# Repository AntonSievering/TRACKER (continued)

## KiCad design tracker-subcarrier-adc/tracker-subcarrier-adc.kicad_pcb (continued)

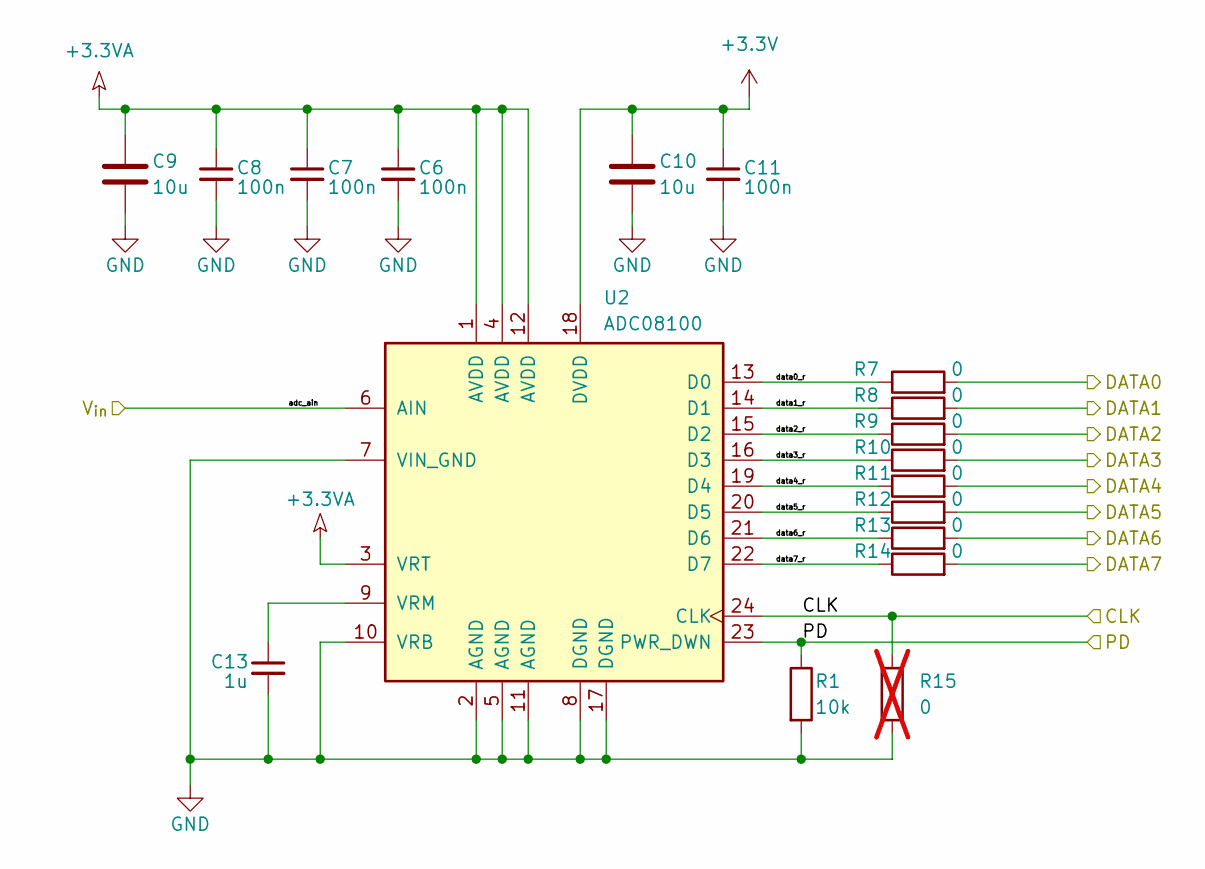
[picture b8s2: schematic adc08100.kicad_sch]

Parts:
C6, C7, C8, C11: 100n; C_0603_1608Metric
C9, C10: 10u; C_0805_2012Metric
C13: 1u; C_0603_1608Metric
R1: 10k; R_0603_1608Metric
R7, R8, R9, R10, R11, R12, R13, R14: 0; R_0603_1608Metric
R15: 0; R_0603_1608Metric; not fitted
U2: ADC08100; TSSOP-24_4.4x7.8mm_P0.65mm; MPN ADC08100CIMTCX/NOPB

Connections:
+3.3V: C10.1, C11.1, U2.18 (DVDD); also elsewhere on the board
+3.3VA: C6.1, C7.1, C8.1, C9.1, U2.1 (AVDD), U2.3 (VRT), U2.4 (AVDD), U2.12 (AVDD); also elsewhere on the board
/ADC I/adc_ain: U2.6 (AIN); also elsewhere on the board
/ADC I/data0_r: R7.1, U2.13 (D0)
/ADC I/data1_r: R8.1, U2.14 (D1)
/ADC I/data2_r: R9.1, U2.15 (D2)
/ADC I/data3_r: R10.1, U2.16 (D3)
/ADC I/data4_r: R11.1, U2.19 (D4)
/ADC I/data5_r: R12.1, U2.20 (D5)
/ADC I/data6_r: R13.1, U2.21 (D6)
/ADC I/data7_r: R14.1, U2.22 (D7)
/IO_PIN_1: R7.2; also elsewhere on the board
/IO_PIN_2: R8.2; also elsewhere on the board
/IO_PIN_3: R9.2; also elsewhere on the board
/IO_PIN_4: R10.2; also elsewhere on the board
/IO_PIN_5: R11.2; also elsewhere on the board
/IO_PIN_7: R12.2; also elsewhere on the board
/IO_PIN_8: R13.2; also elsewhere on the board
/IO_PIN_9: R14.2; also elsewhere on the board
/IO_PIN_10: R1.1, U2.23 (PWR_DWN); also elsewhere on the board
/IO_PIN_MRCC_25: R15.1, U2.24 (CLK); also elsewhere on the board
GND: C6.2, C7.2, C8.2, C9.2, C10.2, C11.2, C13.2, R1.2, R15.2, U2.2 (AGND), U2.5 (AGND), U2.7 (VIN_GND), U2.8 (DGND), U2.10 (VRB), U2.11 (AGND), U2.17 (DGND); also elsewhere on the board
unnamed: C13.1, U2.9 (VRM)

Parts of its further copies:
C12, C18: 10u; C_0805_2012Metric
C14, C16, C17, C19: 100n; C_0603_1608Metric
C15: 1u; C_0603_1608Metric
R2: 10k; R_0603_1608Metric
R3: 0; R_0603_1608Metric; not fitted
R4, R5, R6, R18, R19, R20, R21, R22: 0; R_0603_1608Metric
U3: ADC08100; TSSOP-24_4.4x7.8mm_P0.65mm; MPN ADC08100CIMTCX/NOPB

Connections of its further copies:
+3.3V: C18.1, C19.1, U3.18 (DVDD); also elsewhere on the board
+3.3VA: C12.1, C14.1, C16.1, C17.1, U3.1 (AVDD), U3.3 (VRT), U3.4 (AVDD), U3.12 (AVDD); also elsewhere on the board
/ADC Q/adc_ain: U3.6 (AIN); also elsewhere on the board
/ADC Q/data0_r: R4.1, U3.13 (D0)
/ADC Q/data1_r: R5.1, U3.14 (D1)
/ADC Q/data2_r: R6.1, U3.15 (D2)
/ADC Q/data3_r: R18.1, U3.16 (D3)
/ADC Q/data4_r: R19.1, U3.19 (D4)
/ADC Q/data5_r: R20.1, U3.20 (D5)
/ADC Q/data6_r: R21.1, U3.21 (D6)
/ADC Q/data7_r: R22.1, U3.22 (D7)
/IO_PIN_12: R4.2; also elsewhere on the board
/IO_PIN_13: R5.2; also elsewhere on the board
/IO_PIN_14: R6.2; also elsewhere on the board
/IO_PIN_15: R18.2; also elsewhere on the board
/IO_PIN_16: R19.2; also elsewhere on the board
/IO_PIN_17: R20.2; also elsewhere on the board
/IO_PIN_18: R21.2; also elsewhere on the board
/IO_PIN_19: R22.2; also elsewhere on the board
/IO_PIN_20: R2.1, U3.23 (PWR_DWN); also elsewhere on the board
/IO_PIN_MRCC_26: R3.1, U3.24 (CLK); also elsewhere on the board
GND: C12.2, C14.2, C15.2, C16.2, C17.2, C18.2, C19.2, R2.2, R3.2, U3.2 (AGND), U3.5 (AGND), U3.7 (VIN_GND), U3.8 (DGND), U3.10 (VRB), U3.11 (AGND), U3.17 (DGND); also elsewhere on the board
unnamed: C15.1, U3.9 (VRM)

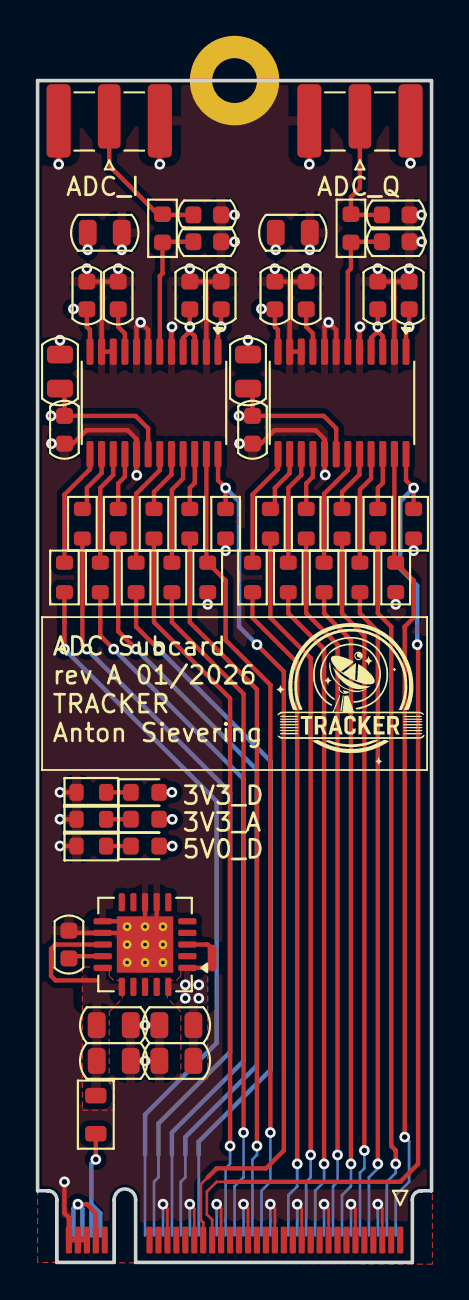
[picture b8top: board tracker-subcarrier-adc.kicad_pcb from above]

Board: 4 copper layers, 22.0 x 66.0 mm, 60 parts (0 on the bottom side), 52 nets.

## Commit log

2026-05-25 TRACKER PCB files to Github
2026-05-25 readme
2026-05-25 added logos, overview
2026-05-27 added pictures
